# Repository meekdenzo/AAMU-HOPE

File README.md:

# AAMU-HOPE (Hands-On PCB Engineering)

Alabama A&M University's Hands-On PCB Engineering program - Learn PCB design through hands-on projects using KiCad

## Description

This repository contains PCB design projects and training materials for AAMU's HOPE initiative. Students learn practical PCB design skills through structured labs and real-world projects using KiCad.

## Repository Structure

```
📁 AAMU-HOPE/
├── 📁 training-labs/
│   ├── 📁 lab-01-basics/
│   │   ├── README.md           # Lab instructions and requirements
│   │   ├── schematic/          # KiCad schematic files
│   │   ├── pcb/               # KiCad PCB layout files
│   │   └── assets/            # Images and documentation
│   ├── 📁 lab-02-components/
│   └── 📁 lab-03-routing/
│
├── 📁 projects/
│   ├── 📁 usb-charger/
│   │   ├── README.md           # Project specifications
│   │   ├── schematic/
│   │   ├── pcb/
│   │   ├── bom/               # Bill of Materials
│   │   └── documentation/     # Additional technical docs
│   └── 📁 light-sensor/
│
├── 📁 resources/
│   ├── kicad-setup.md         # KiCad installation guide
│   ├── design-guidelines.md   # PCB design standards
│   └── component-library/     # Common components and footprints
│
├── 📁 templates/
│   ├── project-template/      # Standard project structure
│   └── documentation-template/# README and doc templates
│
├── .gitignore
├── LICENSE
└── README.md
```

## Getting Started

1. Install [KiCad (Latest Version)](https://www.kicad.org/download/)
2. Clone this repository
3. Start with training-labs/lab-01-basics
4. Follow the README in each project directory

## Contributing Guidelines

1. Create a new branch for your work
2. Follow the project template structure
3. Include detailed README files
4. Submit pull requests for review

## Project Standards

- All projects must include:
  - Complete schematics
  - PCB layout files
  - Bill of Materials (BOM)
  - Assembly instructions
  - Design documentation
  - Test procedures

## Resources

- KiCad Docs: https://docs.kicad.org/
- Recommended Course: https://techexplorations.com/so/kicad-like-a-pro-4th-edition/

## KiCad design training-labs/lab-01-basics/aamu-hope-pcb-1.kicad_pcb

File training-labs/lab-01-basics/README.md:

Please refer to these [instructions](https://drive.google.com/drive/folders/1W4xMZmDtl3gpDHFJ3Kh4LgOIy0SdeQIt?usp=sharing) for this lab.

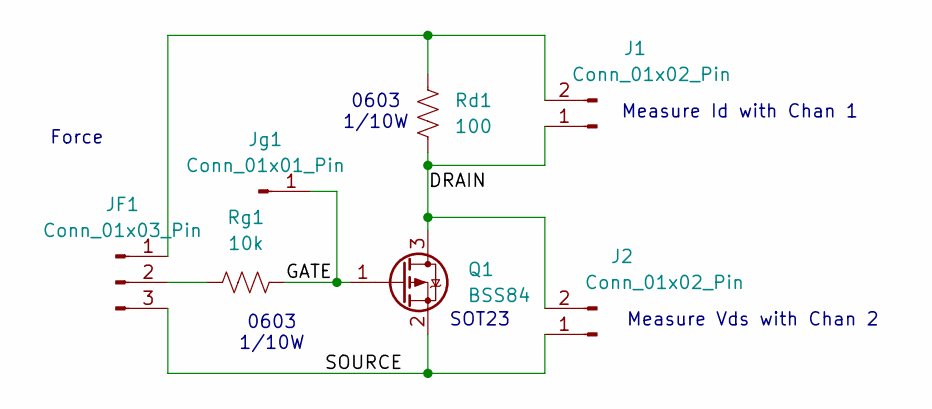
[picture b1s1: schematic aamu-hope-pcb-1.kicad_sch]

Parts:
J1, J2: Conn_01x02_Pin; PinHeader_1x02_P2.54mm_Vertical
JF1: Conn_01x03_Pin; PinHeader_1x03_P2.54mm_Vertical
Jg1: Conn_01x01_Pin; PinHeader_1x01_P2.54mm_Vertical
Q1: BSS84; SOT-23
Rd1: 100; R_0603_1608Metric
Rg1: 10k; R_0603_1608Metric

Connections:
/DRAIN: J1.1, J2.2, Q1.3 (D), Rd1.2
/GATE: Jg1.1, Q1.1 (G), Rg1.2
/SOURCE: J2.1, JF1.3, Q1.2 (S)
unnamed: J1.2, JF1.1, Rd1.1
unnamed: JF1.2, Rg1.1

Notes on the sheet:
0603 1/10W
SOT23
Force
Measure Id with Chan 1
Measure Vds with Chan 2

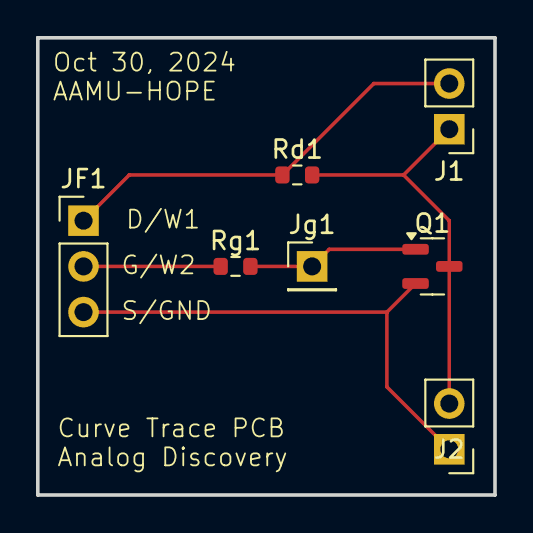
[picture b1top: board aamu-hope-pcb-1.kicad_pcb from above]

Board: 2 copper layers, 25.4 x 25.4 mm, 7 parts (0 on the bottom side), 5 nets.

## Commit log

2024-11-05 initial commit: create repository structure and documentation
2024-11-05 mod: add KiCad file for lab-1
2024-11-22 add `.gitignore` file
